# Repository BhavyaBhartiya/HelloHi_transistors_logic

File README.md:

# HelloHi_Transistors_Logic_Circuit
### In this project, I created a PCB that switches between two words: "Hello" and "Hi," using a bistable multivibrator.

## Simulation

[Link to Demo](https://www.falstad.com/circuit/circuitjs.html?ctz=DwYwlgTgBAZgvAIgMwKgFwM6IAwDpsEECsqYIiSAHAEy4DsAbNUTQIwAsSAnF9g+6hAAjROwFQADiISdUANwiISUALaYlAUwC0rVggB8AKChRgAJSgAPRK2qUoXBlH4OGqeAlZuoAdw-ZUFQBDSzlELgQAeiMTYB8rGztXKCQGe0d3HCiY02hrTyTHKFt7DnF-VEVPAmzjXITkNOTU0rFMhACoKtYa6Lq4hpLisWKkr06Kvtj4-Jbh9hSm8faAqfr8ofGoamxShgmsrptCWti8iiX9lOwF5dhD7pO1gY2xq6HqdgOO09MZi722EW9k+31WOWAaEGXGo2yITg+8JWqAkADsbKghBpjp0VAB7RAAEw0MCCAFcADZoeRYnC4IjMdhcMQ3Mq8ah6KByITkDr0XTsIjYT5C9iUIiMSi-SENJA3OFOObMbwVSTozyY7HVXEEhDE0mU6lc2kIHS4dh0MVIDg7GFIOiUTnc3l4VjirhEFjsXQM5iWgTPf4IHaA64LZXIwPQ2HKsPFfaRiEAc1lTWodFhcyQO0T-XOnhhCuKhaQqWRR214LzsvlsblC1LKoeOKr02jKVSxczaVzbdm8sbcZavb+NYbTS+QOH9x+zwwDUnwKgRFswPLEgxqhUiDQEDJGmlQdYJaaRWnkwh8-yWmzS7PPZnnQ3Gq3O73B+eFmvt7mN8zOZnLxUD8Q5glCJRpS-JRVzmFd-2+IDfFVMCwgQEhngAGQAUQAEQaLQmHHewCJcc9QN1fVySpLQKQ0QlBG6QQk0OYRQJ5OlsD0TDcPwhgMyXLQ6Bgh9kIokkqLQGi6IYzcQGYn4oFYhSVHYvlOOlbC8OvCVFSaAivDXR9AjEg1qNo+jFMYxT5M6JTcVUvB1O4rTEEEnYBIzKc7HLfEiXEw0pIskArLkljpHsl18C4iFNPwzztn4tygWobMfJMiTApkl9QoUuzAgcqKNJ4694uzIEku2SgwWMvzTMk8yss5HLbPC-LIqcmLitc+LWEYKAKtYMsjNUdKAoayzZJswRWtUAqOv6WKSvcoYKqqtLaoy8bgsmsK2Pa6KFq6014uoT5+p6yhynIjaxukibsqmxSZpU-aipc01uG7YjOEzBl1r1fyzLu7aHt25S5oO2JFtcn6UhGLQLXg-7KNuoKQsevLZte5z8LFKdVwRop02oZHAfq4H0bBiKOMh0xodNJknGoFxCaZz5SbqzL7qajHnoht7caJgyEcoUpGA5zaKZ23K+exzr3pFoEvG+lwSgl1HGqYqm2ppgXr3YM6egWG9LqgUX1aBtHpZavbdZx-X4VGb7byNi3yat0GZdttTaeAembxGX8qCIt2uZBnntaxu35fwuski0Ox7CQP7ht8gHOa2ymvfBuXDoV6gzwZfrBzI5TRstzXrMjl7o7z2Pb0T-q4+qkabor7mtez6mfb11zTvDL4m4btbU-L93K+a6bvcc33-f7rsm7OlKSdHtvx47quu51nv7b7sV5kX25LtDzPrannPa6ho6E6q4p5QT-fBqbMu17DrObYvneY+-JJRabv-Xar3TpLD2Ect5Ry-nXb8fU-43k7ObIBKN27h07h-buM9Dy8TOr+QicMrqzghEGAi-EcEkLaEZKMS0px6T4pmG4I4XiuVoXg-qzD6wMKIbgpA8MuH0IoYQrBDZ75sL4RefoRDSruWIXQ-BrZRxUISrCAit9iYcN4ioxKzDVH8PEbxfixNWEkNEVkSh3V3Lz2kdsdmOi+xMP0WdSx2ixG2OOstPqljerPzkYw00zDPGGJjIhZx8izFK3jn47yNiQm+P4itPx4sok+MccLLR1jglJJ6p2ZRpQhrpM4QArJaR7Ajzyeo4p5V4olJMQIhRbpjZFOKMfRJ+TSim2ycUXJ1TdEKOXqwv+y81HXgab09pdTBmhMquVYZVSCHdKYf02+7SBnNLiu5bMxEGBnkiaUoZWyNkLOqqY46wkNl7PGb40iNCzkrKGQZHB1ydmuQZNQ4izyoAG1kZg7S7kPlNwIO8tJXSXE6ELMrJ28ZDk1NcseWEYKE7-I+QwlMCjFnxSRDcp5fVSEyPOVoN5v4dKGUeR9GBxFUjJSCUC6JAciLFyuByLxXy+6FyUeS7YlLZnArjmS+lHLvFEN6Y3G8vLGVHITkvQewqKWiqhaaeeMK6XStxZ8Voxs2UMuVbfI2ir2UyrmR9X+PKlUYoZobe+6q+VMoZo7FaFq9XArxvGI1urcWM11TqjVJrWbbBZna11t9rSspFa6n88M-Ves+gJcN6TkUw1VvHRGoxIX9FjQzF298WRmylIk1NJsFiwODlADMSL8KDgLZ2YtObY4APvnYIECCY2x0flk3pasq3XnlW0kMxQEmNo7UvW88KQSpXbX3Ye5UGWVWzX2vujsypN0Ho2EtHa-7JyUXWolVLgC5pLnpdZKQYTLtcoWoOptPpHrTb9JRYgk4iS3bmxN86RZJ06Zy0wD6iaJTeU4+9gs2bG2-YCt927cYAPcaKCFuKFVwug4er1sGg3GuJVoKqU53GUDPLYC9WhmT5uIrh5wnyxWXTQ04HDazX38vwqLJO7iYRTko1anDnZ7Rkfox2e11L2ODhw6uROuKCM8e44xsVXA+OwLEzGL4AmRhCsk1OgTfHJXyZhTJge5V5OgkU7CwsvHYXkOQwRhVemuzaazf1AjDat1EJU-DeTVngM2ZGGUCzq4yi4ow-+-qnntgjuQz5p+3mihjK9UZrJAWROypQ8FtpPn+5qcacbALTT-NE0HXFmZVHrwEZGXFvz1nqNE0WT5wNAnazFaK8m4FOXFm8HDJlpjgn44law16y6ScCYtZXv5-ea7vO9da6lxURdouKkGwV7Lgd0OYe6xN1yJXpvDdm456jvX0O9ZTuk-2OXB1Gbg6JV+p9PZoO3hg3epowtsZGA5nUh2pbHfPugwq52cPObaUZgz11gEaw3pPJ609nvf1ck1-Dsmbs1W+8g9+j3TuA6gcDsHGnZPScQWTN+Z9-ufzO0Di7U2rsNkY63SH68UGbxOxA7H8PTSoZSOt0jJ97tgPJzXSBV8FYLbYyx3tX2kEk+h5jp7802erdo2RmjtPGVE95+jh7AvYdC+pW835glCw-VxXQVX6X-msYvR8WJSR2HwewD+NpugDcARnaaXQfUig6H8ZW5DPQSGm9YEXbhRGotm6nC7t3n2VvXl0E0Qtdvfce-1SHzM8MBThgyPB-x7v+o+kj2H4F0fti27TyqqD-iC5kcz7Hx3LmVWJ6LzUOPfVi92+R9OubVvS-lTT675bWXoU5-+VX8MZfC8jAz-4gvteO-FBG2n-v-vW99SbyX5zm2B9m+HUouf2wUeF7GFHzY+3Z-+Jc3b1fKfqWL+M4v5ZheJ+6YPxvsfdekighL9f8HYrrdM0lUf5fm+7-EUX2VbPnYhVH-v57nPWBXQH-f-cPR-DjW-JOC3WfXYLyBvIYL-I3ANK4HQWAlIaAy-HfW9eA83KrffePF3XA7PA3Qg7AqDNA4PHoZAvAv2a+cAm-O3CvLvHnNHI7JnGHCnOHYXAPLfNfG3SXNOaXNg1BDglnSnbg8fBEM-LfGfF+YnGXdguXTghXWghWcAnjeg0fW7eQ4QsnUQ-mF7egoAnPMUBnUBEQpQsQrgumOggg42dQv3bQoQxnCwzGKwlQ-2HoE3ew7AZ3T5KXVglwvQywgwnHLAlIF3IPFLFgjOIIv7Nw0IqnVAgNQg73fwwQwI8w4IhI3OCQq3NAyvL3JfGvOQ5wrI+I2WS+GwtQj4feO3NMUw1HWI8o3mAHDwug43KTD-XwroswieVorHawpJKg5KOoz-DAlvK-EEMYhAiYpjLwroyA9AmgohIowo+vcg-RGY2TZgzAwPaYj-DYxJTwtA3vdyLQiHMo-o6uRIvI8I3vU8AQseBQ1wyo1nao-CBY5IVA-iC4gI5o648Bdw32VYoYM41pPfYY04vPdfZveYzo748-OEh-TYUg0zOPR4kvfg4goEXvbEo3X4mE-E5DDXWEWGVA28Fkcg7wxPBEqk44ug+dWMHQdVdFA7HQuIgYwXWeRktMR2HQL4EENkmIkBQE5nW4j4gPAxZkwaPjYU0ozIsU-Q3IyU6Fb0RUM-dUlIWQpwxU37Lk+XHktQrU3PRPE0+U3UgE-Um4lU1Qz4rUhPAUu5YxBUq00nCotoo0+0gyHYBvLUu4dkq460oEiUu0gPf04ff0l0y00U4M8U20zwk0sYk03YPouM5Uqo4Yh0++QaM9aM+Yh04fSNNdbDDgAybVJ0pwBrZ4XNWwVWHM5mfNFYz4xs7UhfRuEs+DVs7tHQU0kMKDU0isus24fMh-VsrYXs4LBMBktQ7ssY7s1Mpo2M90g05Qr0qU1WYfcc-M-45c-nHIzMzwhchvcc6cwMvUlcm0w8ug1sx04csMNMy8kMhMm8lwU03st8i0y4i8-ct48Q1Uq3W8s-W8nU78t038z0+Y1jd5Z-Ok1-PY-0lA3M24M82fFMj-Qtfs+DQUosSshUKDHCmUzCxcx3YijC02AM2fE9HMwir8h-YsosvMyE1Y28hss8Ucz3Dsrc9i5ilsnixPbsuiziz8vPPski2fMSj-Qc1CvY6Sk84LDisAqM+wwtQBUiiinM1S0C+iuU0SomcSvY1kvPMigiu5M-PrYOAc0icyt3aIhCu5KPCyuyyYj8hsRy2y3i8Mn0jPJyzy6Fbsnyjygc-RfkwaIK+DJk0K3yqDJUKK8Kx3JMjC+KtCn09vMKzMZy+YucpKjKvywCt8tK6KrszchfIqhK8sos5KwyvqTNFkqqly5CofUqiimSyY5hIoPxRSlxNINIotAcbZWvfgXEpwOgfqkoyY0k5IUahsAay-Salzaa9A8aq1eawsRa9Zc5Iag+da2atqweBVHa5ao5YZf5Q685OgH-U6sa8602X0vqmao62VSam-M6k1Lal666k1Z6v+V64ld6n6z64lSawcX6waxdCtQGwa-SoEPxbSp6nYoERgJWOG-VZhfedqzjHxLa9G-iRooG94eUJG95R6-VImyfMmrq6JZ60694FGlxIm4vam5s-ISUdPEa+lPG2vZ6-eBmzmy-BgN8jqrYkm7q4WwjEEXYtq2JIuTqvK-gCWmG6W5E2VeW7Yf5d6yWq1LayfWG5W1G-a+UWWhhemYGitQsXPR8iCwY9o96bmxG82zW3cn7J8+M682282n682vmmM52q27k3uBAeakYeancjI8CjHA894sMxASaooSa72sCvciOv8oYk20FNa0FUCp2qHZOyCo5EOhYCmvKomnm1XEWqmzO2EMmumiumMOOtMC4mshoeO+wbmi9bG+wd6uWweU0gWmPTGoMLuzu4W42o6bWwsbWrOsOpO2XSO-86OhALajqweBO7OvnXO629cxAbWkYbW0O543Qj0zegO-6zunu1e6e32je-287LumGnux2y+nO2elOm2hoLawcd6v4p+9el+vOnHB0TvRGhGy26+w0k+-pdW-eX00Bv+4+87C6pmdW6G2BxQue1Oo6HoM6R2LgU2L8tel47I1+rehAGEewR2cXfBn+who+m+nHLgPqHBzsKhg+zkq8qO+mBhxUc4ljOYghw+1c4EgOsh5YrNKAluahgR9h+e+mLBma3Es9PhyRth58t2hoRwKceUDRn1dI1hlo6RjB96bR7tbR5WVB14-+qnYxnB4NJcq+uBuhqx94VcbRh3EU+xtB4h4R94K4UxpRvRpUkI201NShqs1dPWlxVx2EcXNxy-GJ6Jv+IS-VcXedcXH9S-YxlwNJ-gc5bJvDEEWJyY4xgyNJy1I5UpsJkEHJk1UxpocXMxk1epup-pMp2VPx+tABOY8pzpjpvYcunxep9yeJ85LgZhyppNEZvB8Z2wZm8IXh3pnRyZ+RsRxZmp3AhwA3GunxLh0RnZ8lEZrFXxzZiJ6JOR0Rs5-Zk1C53xw52Z0hq4esBwW5kZ+lHB45l55KXYDZpOLZoMWp3E55mp5x2EPZ1qq1ERmxpWcbDJxhpwUx6FyYs5yF4oBFq1OYLYIgZzMFo5TFlCoEXFg9E5nxAlyNHqiIuWlIhYERzssRYASIcACAIwIAA)

## Schematic

## PCB

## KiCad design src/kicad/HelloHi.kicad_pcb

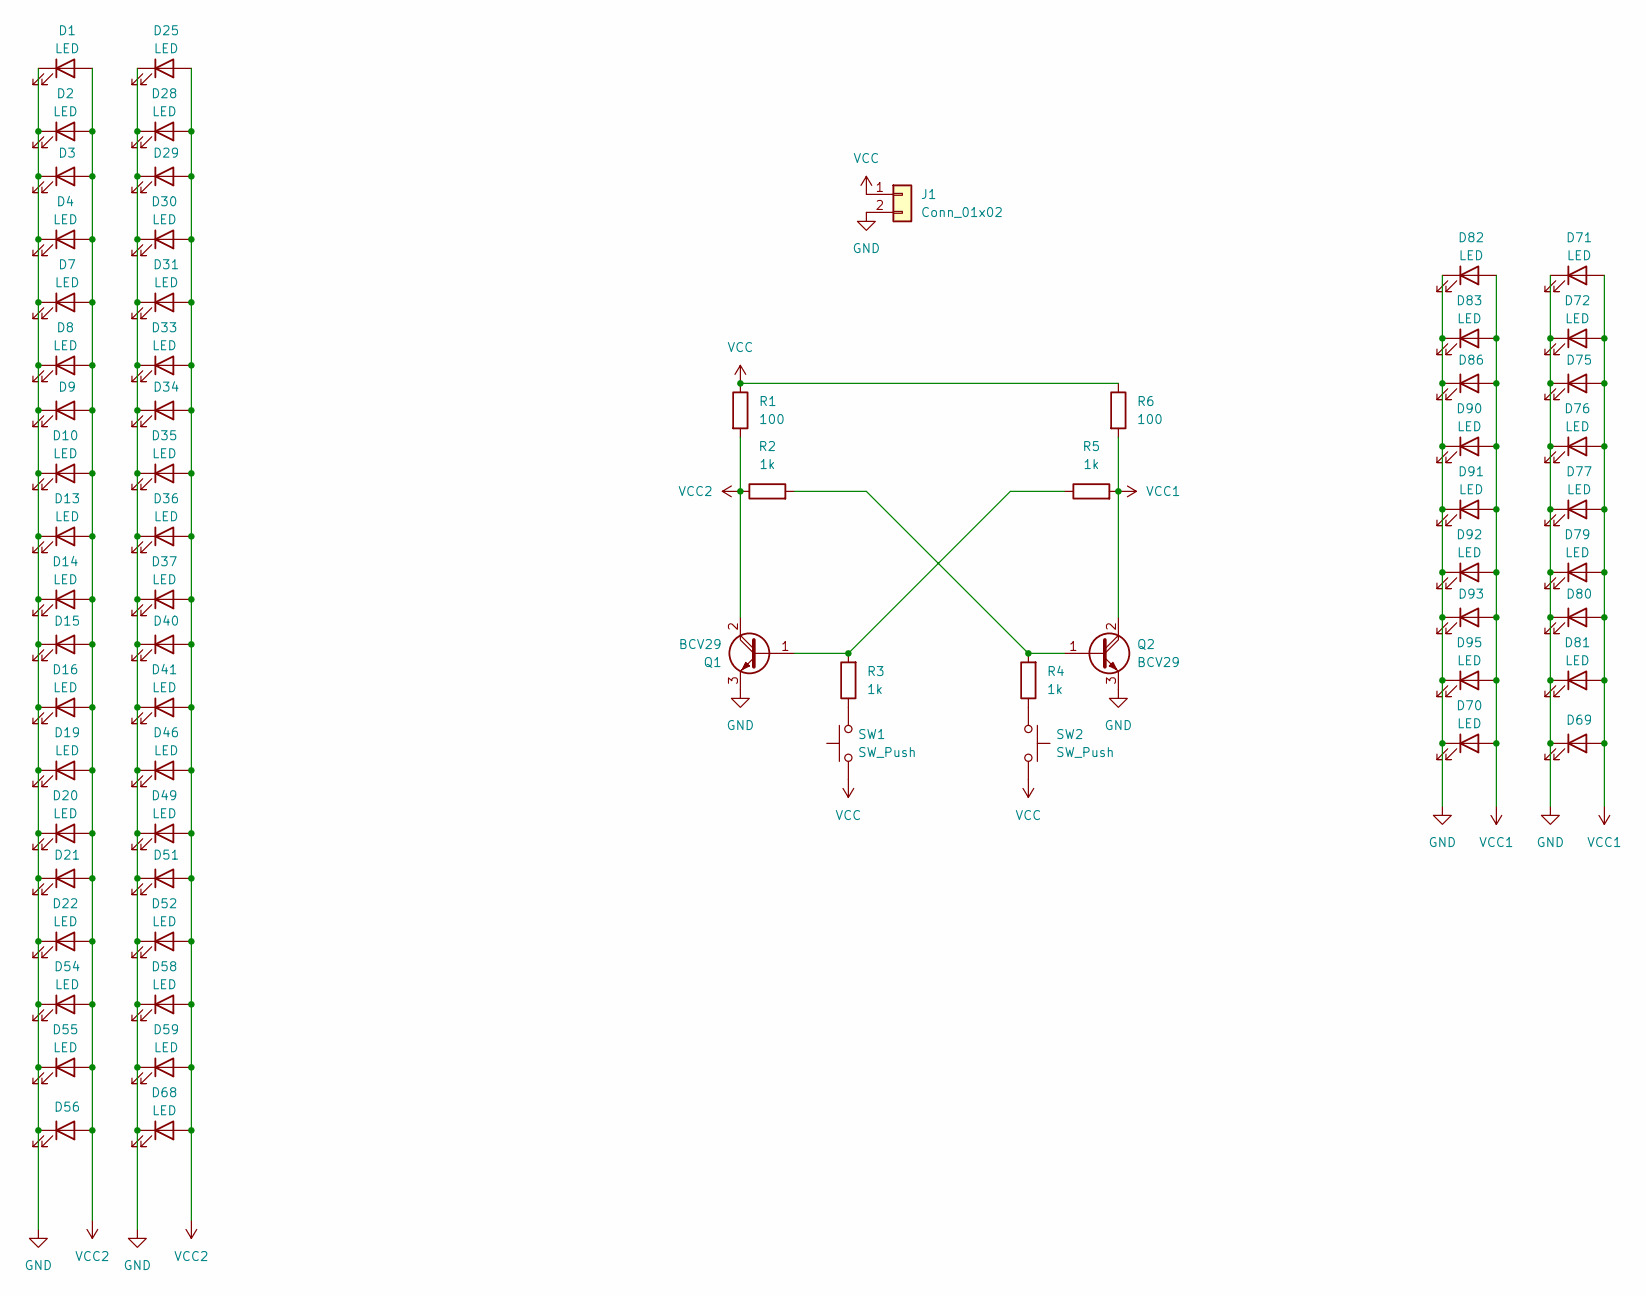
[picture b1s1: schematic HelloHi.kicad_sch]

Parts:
D1, D2, D3, D4, D7, D8, D9, D10, D13, D14, D15, D16, D19, D20, D21, D22, D25, D28, D29, D30, D31, D33, D34, D35, D36, D37, D40, D41, D46, D49, D51, D52, D54, D55, D56, D58, D59, D68, D69, D70, D71, D72, D75, D76, D77, D79, D80, D81, D82, D83, D86, D90, D91, D92, D93, D95: LED; LED_D5.0mm
J1: Conn_01x02; PinHeader_1x02_P2.54mm_Vertical
Q1, Q2: BCV29; TO-92L_Inline_Wide
R1, R6: 100; R_Axial_DIN0204_L3.6mm_D1.6mm_P7.62mm_Horizontal
R2, R3, R4, R5: 1k; R_Axial_DIN0204_L3.6mm_D1.6mm_P7.62mm_Horizontal
SW1, SW2: SW_Push; SW_PUSH_6mm

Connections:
GND: D1.1 (K), D2.1 (K), D3.1 (K), D4.1 (K), D7.1 (K), D8.1 (K), D9.1 (K), D10.1 (K), D13.1 (K), D14.1 (K), D15.1 (K), D16.1 (K), D19.1 (K), D20.1 (K), D21.1 (K), D22.1 (K), D25.1 (K), D28.1 (K), D29.1 (K), D30.1 (K), D31.1 (K), D33.1 (K), D34.1 (K), D35.1 (K), D36.1 (K), D37.1 (K), D40.1 (K), D41.1 (K), D46.1 (K), D49.1 (K), D51.1 (K), D52.1 (K), D54.1 (K), D55.1 (K), D56.1 (K), D58.1 (K), D59.1 (K), D68.1 (K), D69.1 (K), D70.1 (K), D71.1 (K), D72.1 (K), D75.1 (K), D76.1 (K), D77.1 (K), D79.1 (K), D80.1 (K), D81.1 (K), D82.1 (K), D83.1 (K), D86.1 (K), D90.1 (K), D91.1 (K), D92.1 (K), D93.1 (K), D95.1 (K), J1.2, Q1.3 (E), Q2.3 (E)
unnamed: Q1.1 (B), R3.2, R5.1
unnamed: Q2.1 (B), R2.2, R4.2
unnamed: R3.1, SW1.2
unnamed: R4.1, SW2.1
VCC: J1.1, R1.1, R6.1, SW1.1, SW2.2
VCC1: D69.2 (A), D70.2 (A), D71.2 (A), D72.2 (A), D75.2 (A), D76.2 (A), D77.2 (A), D79.2 (A), D80.2 (A), D81.2 (A), D82.2 (A), D83.2 (A), D86.2 (A), D90.2 (A), D91.2 (A), D92.2 (A), D93.2 (A), D95.2 (A), Q2.2 (C), R5.2, R6.2
VCC2: D1.2 (A), D2.2 (A), D3.2 (A), D4.2 (A), D7.2 (A), D8.2 (A), D9.2 (A), D10.2 (A), D13.2 (A), D14.2 (A), D15.2 (A), D16.2 (A), D19.2 (A), D20.2 (A), D21.2 (A), D22.2 (A), D25.2 (A), D28.2 (A), D29.2 (A), D30.2 (A), D31.2 (A), D33.2 (A), D34.2 (A), D35.2 (A), D36.2 (A), D37.2 (A), D40.2 (A), D41.2 (A), D46.2 (A), D49.2 (A), D51.2 (A), D52.2 (A), D54.2 (A), D55.2 (A), D56.2 (A), D58.2 (A), D59.2 (A), D68.2 (A), Q1.2 (C), R1.2, R2.1

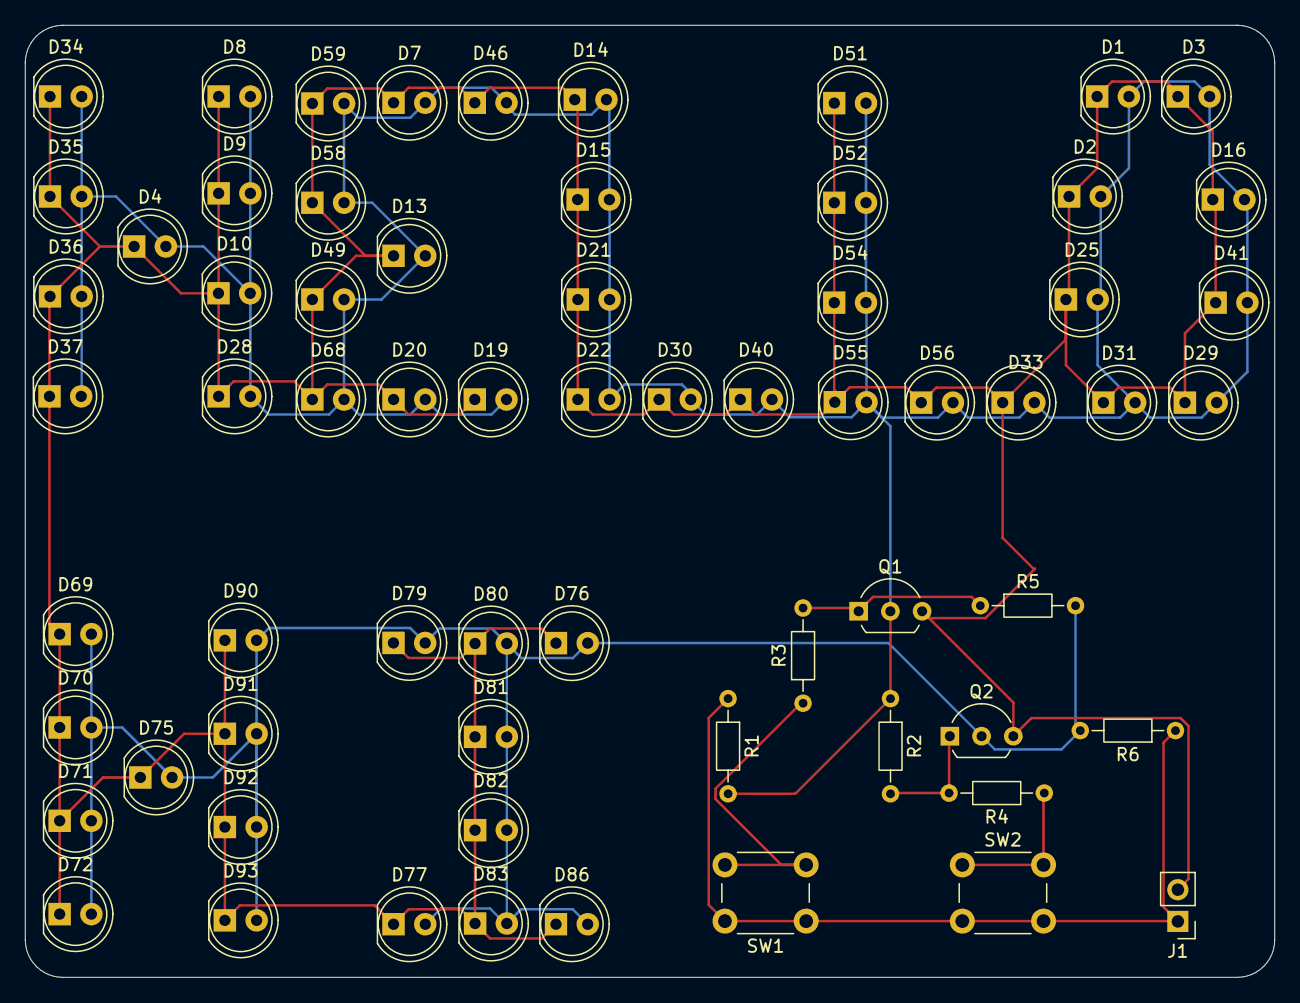
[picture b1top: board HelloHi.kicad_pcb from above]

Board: 2 copper layers, 100.0 x 76.2 mm, 66 parts (0 on the bottom side), 8 nets.

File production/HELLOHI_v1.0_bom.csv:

Designator,Footprint,Quantity,Value,LCSC Part #
"D1, D10, D13, D14, D15, D16, D19, D2, D20, D21, D22, D25, D28, D29, D3, D30, D31, D33, D34, D35, D36, D37, D4, D40, D41, D46, D49, D51, D52, D54, D55, D56, D58, D59, D68, D69, D7, D70, D71, D72, D75, D76, D77, D79, D8, D80, D81, D82, D83, D86, D9, D90, D91, D92, D93",LED_D5.0mm,55,LED,
J1,PinHeader_1x02_P2.54mm_Vertical,1,Conn_01x02,
"Q1, Q2",TO-92L_Inline_Wide,2,BCV29,
"R1, R6",R_Axial_DIN0204_L3.6mm_D1.6mm_P7.62mm_Horizontal,2,100,
"R2, R3, R4, R5",R_Axial_DIN0204_L3.6mm_D1.6mm_P7.62mm_Horizontal,4,1k,
"SW1, SW2",SW_PUSH_6mm,2,SW_Push,

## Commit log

2026-04-08 Create a
